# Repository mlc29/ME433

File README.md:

# ME433

This Marcus Cisco's repository for ME433 Projects and HWs.

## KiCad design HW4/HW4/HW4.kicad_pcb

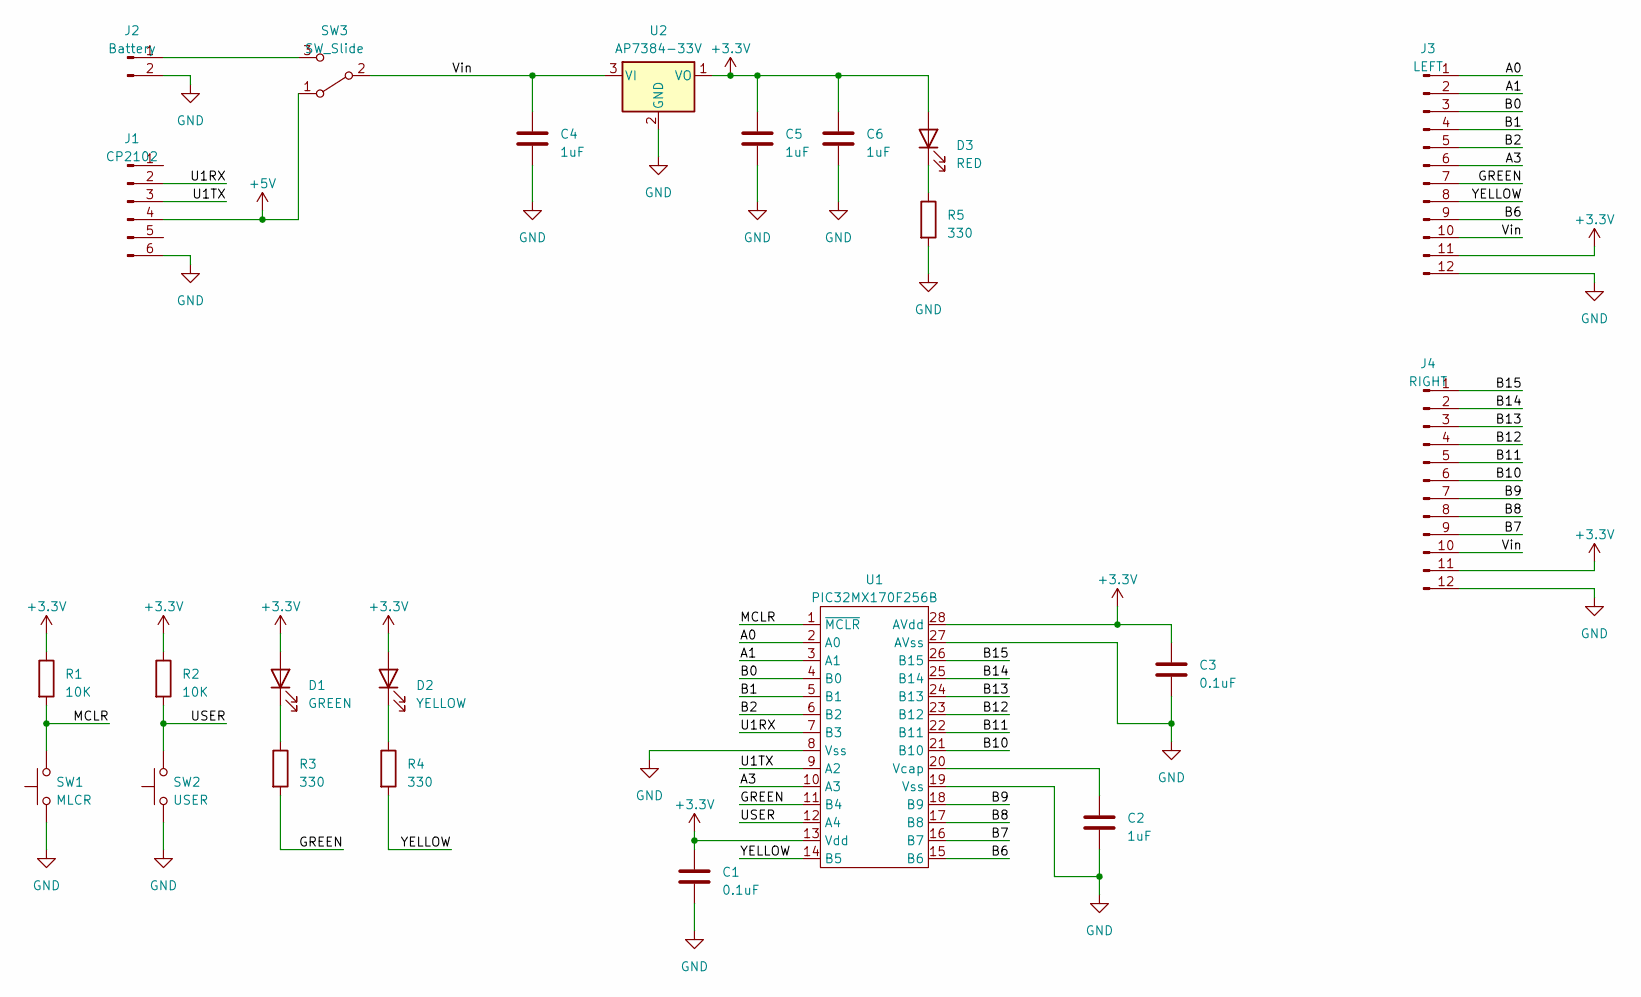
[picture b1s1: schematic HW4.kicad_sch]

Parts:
C1, C3: 0.1uF; C_Disc_D3.4mm_W2.1mm_P2.50mm
C2, C4, C5, C6: 1uF; C_Disc_D5.1mm_W3.2mm_P5.00mm
D1: GREEN; LED_D3.0mm
D2: YELLOW; LED_D3.0mm
D3: RED; LED_D3.0mm
J1: CP2102; PinSocket_1x06_P2.54mm_Vertical
J2: Battery; PinSocket_1x02_P2.54mm_Vertical
J3: LEFT; PinSocket_1x12_P2.54mm_Vertical
J4: RIGHT; PinSocket_1x12_P2.54mm_Vertical
R1, R2: 10K; R_Axial_DIN0207_L6.3mm_D2.5mm_P7.62mm_Horizontal
R3, R4, R5: 330; R_Axial_DIN0207_L6.3mm_D2.5mm_P7.62mm_Horizontal
SW1: MLCR; Push_Button
SW2: USER; Push_Button
SW3: SW_Slide; Slide_SW2
U1: PIC32MX170F256B; DIP-28_W7.62mm_Socket
U2: AP7384-33V; TO-92L_Inline

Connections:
+3.3V: C1.1, C3.1, C5.1, C6.1, D1.2 (A), D2.2 (A), D3.2 (A), J3.11, J4.11, R1.1, R2.1, U1.13 (Vdd), U1.28 (AVdd), U2.1 (VO)
+5V: J1.4, SW3.1 (A)
/A0: J3.1, U1.2 (A0)
/A1: J3.2, U1.3 (A1)
/A3: J3.6, U1.10 (A3)
/B0: J3.3, U1.4 (B0)
/B1: J3.4, U1.5 (B1)
/B2: J3.5, U1.6 (B2)
/B6: J3.9, U1.15 (B6)
/B7: J4.9, U1.16 (B7)
/B8: J4.8, U1.17 (B8)
/B9: J4.7, U1.18 (B9)
/B10: J4.6, U1.21 (B10)
/B11: J4.5, U1.22 (B11)
/B12: J4.4, U1.23 (B12)
/B13: J4.3, U1.24 (B13)
/B14: J4.2, U1.25 (B14)
/B15: J4.1, U1.26 (B15)
/GREEN: J3.7, R3.2, U1.11 (B4)
/MCLR: R1.2, SW1.2, U1.1 (~MCLR)
/U1RX: J1.2, U1.7 (B3)
/U1TX: J1.3, U1.9 (A2)
/USER: R2.2, SW2.2, U1.12 (A4)
/Vin: C4.1, J3.10, J4.10, SW3.2 (B), U2.3 (VI)
/YELLOW: J3.8, R4.2, U1.14 (B5)
GND: C1.2, C2.2, C3.2, C4.2, C5.2, C6.2, J1.6, J2.2, J3.12, J4.12, R5.2, SW1.1, SW2.1, U1.8 (Vss), U1.19 (Vss), U1.27 (AVss), U2.2 (GND)
unnamed: D1.1 (K), R3.1
unnamed: D2.1 (K), R4.1
unnamed: D3.1 (K), R5.1
unnamed: J2.1, SW3.3 (C)
unnamed: C2.1, U1.20 (Vcap)

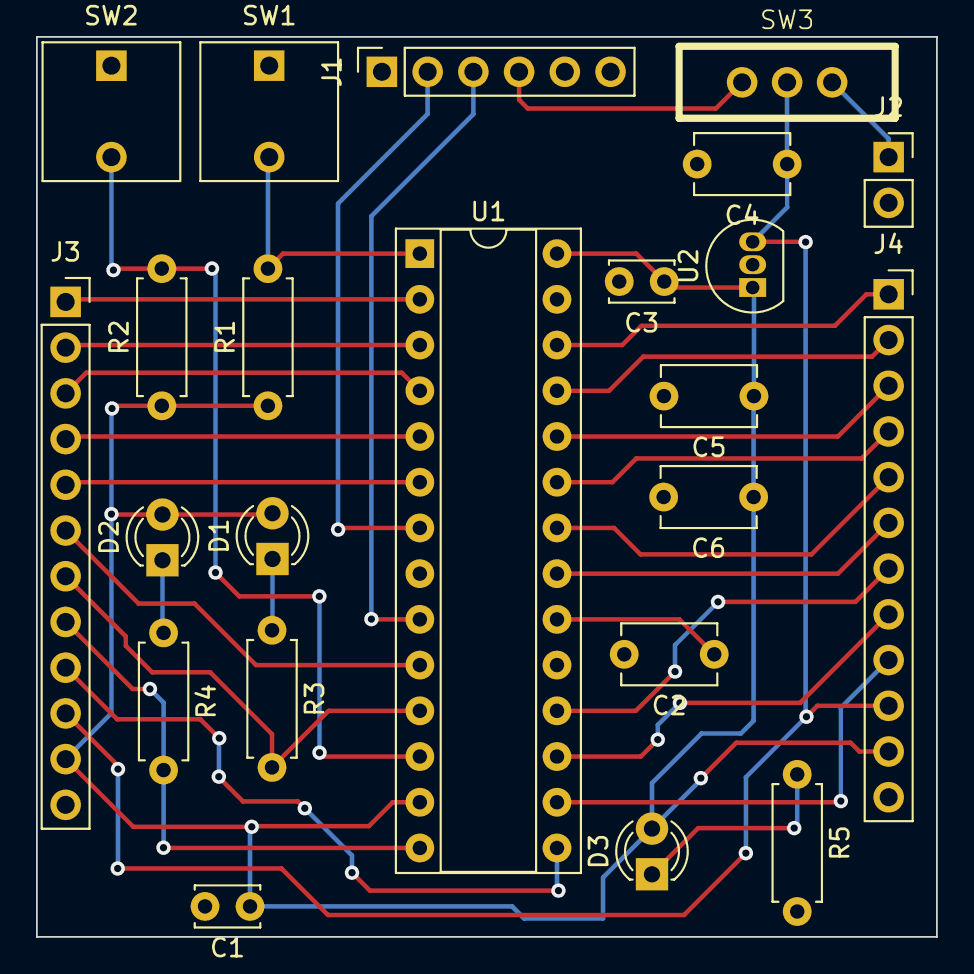
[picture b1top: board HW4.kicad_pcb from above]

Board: 2 copper layers, 50.0 x 50.0 mm, 23 parts (0 on the bottom side), 31 nets.

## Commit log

2023-04-02 Create HW2
2023-04-04 Partial HW2 update
2023-04-07 HW2 complete
    Finished code for HW2
2023-04-07 HW2 repository update
2023-04-09 Correction
    Corrected HW2 code and started HW3
2023-04-09 Refresh of HW2
2023-04-09 HW3 Code template started
2023-04-13 HW3 Update
2023-04-13 HW3 to repo
2023-04-17 HW4 Update
2023-04-27 HW5 Complete
2023-04-30 HW6 Start
2023-05-02 HW6.1
    Started HW6 with I2C. Got the PIC led heartbeat going and able to blink GP7 output.
2023-05-02 HW6.2
    Updated with generic i2c write function
2023-05-02 HW6.3
    Added i2c generic read function
2023-05-02 HW6.4
    HW6 Complete
2023-05-02 HW6 video
2023-05-03 HW7.1
2023-05-03 HW7.2
    Template code complete and working
2023-05-03 HW7 Plotter included
2023-05-03 HW7.4
    HW7 Finished with screenshots
2023-05-03 HW8.0
    Setup with all files
2023-05-03 HW8.1
    Started code for OLED screen
2023-05-04 HW7 fix
    Fixed HW7 to print 0x68
2023-05-04 HW8.1
    drawChar function complete. Prints "Hello World!"
2023-05-04 HW8.3
    Code finished and working
2023-05-04 HW8.4
    Video added
2023-05-04 HW8.c added to HW8
2023-05-04 HW8.5
    updated drawMessage to rollover
2023-05-08 HW9.1
    HW9 files downloaded and stored
2023-05-09 HW9.2
    Assignment up to 9_5 done
2023-05-09 HW9.3
    Assignment complete through 9_6
2023-05-09 HW9.4
    HW9 complete
2023-05-11 HW10.1
    HW10.X created and sample code added
2023-05-11 HW10.2
    Code is essentially filled in. LEDs turn on, but cannot be changed or turned off by hardcode. Need to find source, possibly in if statements of ws_setColor?
2023-05-11 HW10.3
2023-05-14 HW10.4
    HW10 rainbow complete. Still messing with for loops for more readable code
2023-05-14 HW10.5
    HW10 complete. First LED doesn't want to play nice though.
    Could play with changing the delay to match numLED, or leave it up to the user
2023-05-14 HW10 complete
2023-05-14 Better HW10
2023-05-16 HW11
    HW11 complete
2023-05-28 HW13 Done
2023-05-28 HW14
    Finished HW14
2023-06-08 HW15
